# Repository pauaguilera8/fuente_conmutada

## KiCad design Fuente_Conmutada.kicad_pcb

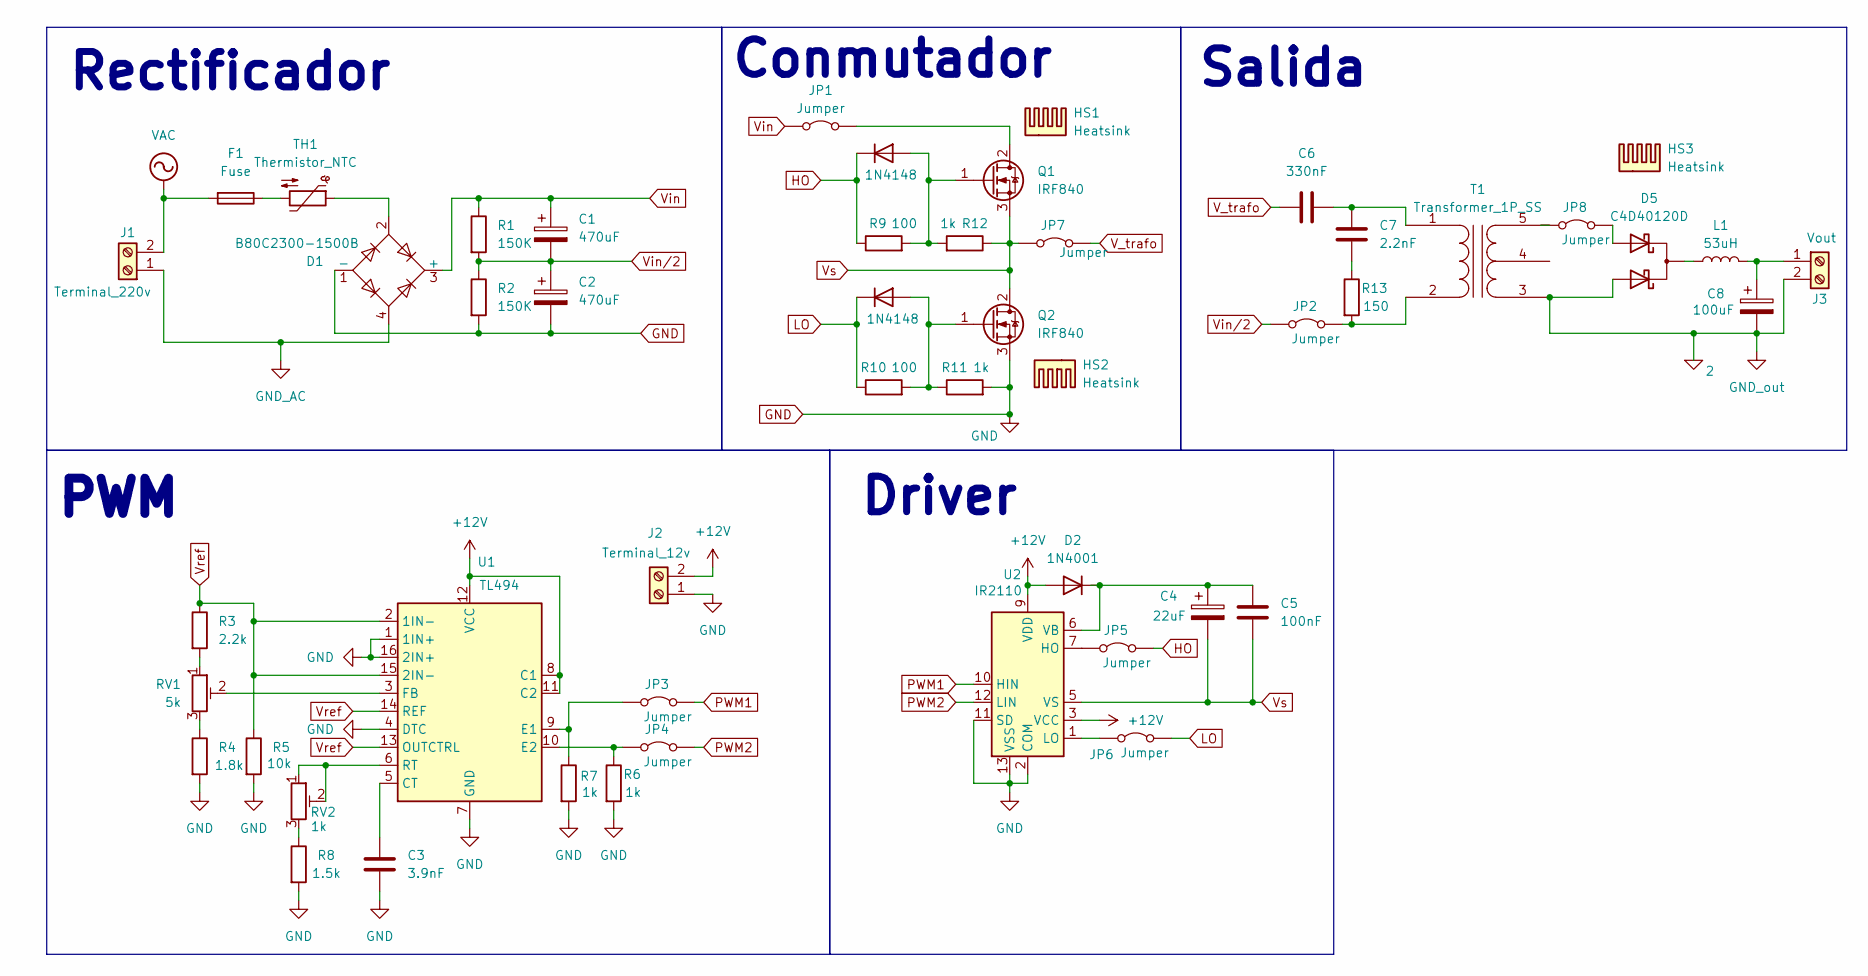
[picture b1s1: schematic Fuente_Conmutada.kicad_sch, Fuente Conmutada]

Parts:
C1, C2: 470uF; CP_Radial_D17.0mm_P7.50mm
C3: 3.9nF; C_Disc_D5.0mm_W2.5mm_P5.00mm
C4: 22uF; CP_Radial_D5.0mm_P2.00mm
C5: 100nF; C_Disc_D5.0mm_W2.5mm_P5.00mm
C6: 330nF; C_Disc_D5.0mm_W2.5mm_P5.00mm
C7: 2.2nF; C_Disc_D5.0mm_W2.5mm_P5.00mm
C8: 100uF; CP_Radial_D10.0mm_P5.00mm
D1: B80C2300-1500B; Diode_Bridge_Vishay_KBPM
D2: 1N4001; D_DO-35_SOD27_P7.62mm_Horizontal
D3, D4: 1N4148; D_DO-35_SOD27_P7.62mm_Horizontal
D5: C4D40120D; TO-220-3_Vertical
F1: Fuse; Fuseholder_Cylinder-5x20mm_Stelvio-Kontek_PTF78_Horizontal_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
HS1, HS2, HS3: Heatsink; Heatsink_Stonecold_HS-S02_13.21x9.53mm
J1: Terminal_220v; TerminalBlock_Altech_AK300-2_P5.00mm
J2: Terminal_12v; TerminalBlock_Altech_AK300-2_P5.00mm
J3: Vout; TerminalBlock_Altech_AK300-2_P5.00mm
JP1, JP2, JP3, JP4, JP5, JP6, JP7, JP8: Jumper; PinHeader_1x02_P2.54mm_Vertical
L1: 53uH; L_Toroid_Vertical_L22.4mm_W10.2mm_P7.90mm_Vishay_TJ4
Q1, Q2: IRF840; TO-220-3_Vertical
R1, R2: 150K; R_Axial_DIN0207_L6.3mm_D2.5mm_P10.16mm_Horizontal
R3: 2.2k; R_Axial_DIN0207_L6.3mm_D2.5mm_P10.16mm_Horizontal
R4: 1.8k; R_Axial_DIN0207_L6.3mm_D2.5mm_P10.16mm_Horizontal
R5: 10k; R_Axial_DIN0207_L6.3mm_D2.5mm_P10.16mm_Horizontal
R6, R7, R11, R12: 1k; R_Axial_DIN0207_L6.3mm_D2.5mm_P10.16mm_Horizontal
R8: 1.5k; R_Axial_DIN0207_L6.3mm_D2.5mm_P10.16mm_Horizontal
R9, R10: 100; R_Axial_DIN0207_L6.3mm_D2.5mm_P10.16mm_Horizontal
R13: 150; R_Axial_DIN0207_L6.3mm_D2.5mm_P10.16mm_Horizontal
RV1: 5k; Potentiometer_ACP_CA9-H2,5_Horizontal
RV2: 1k; Potentiometer_ACP_CA9-H2,5_Horizontal
T1: Transformer_1P_SS; Ferrite_Core_Trans
TH1: Thermistor_NTC; R_Axial_DIN0207_L6.3mm_D2.5mm_P7.62mm_Horizontal
U1: TL494; DIP-16_W7.62mm
U2: IR2110; DIP-14_W7.62mm

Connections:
+12V: D2.2 (A), J2.2, U1.8 (C1), U1.11 (C2), U1.12 (VCC), U2.3 (VCC), U2.9 (VDD)
/Punto_medio: JP2.2 (B), R13.2, T1.2 (AB)
GND: C2.2, C3.2, D1.1 (-), J2.1, Q2.3 (S), R2.2, R4.2, R5.2, R6.2, R7.2, R8.2, R11.2, U1.1 (1IN+), U1.4 (DTC), U1.7 (GND), U1.16 (2IN+), U2.2 (COM), U2.11 (SD), U2.13 (VSS)
GND_AC: D1.4, J1.1
HO: D3.1 (K), JP5.2 (B), R9.1
LO: D4.1 (K), JP6.2 (B), R10.1
unnamed: C7.2, R13.1
unnamed: C1.1, D1.3 (+), JP1.1 (A), R1.1
unnamed: D1.2, TH1.1
unnamed: C4.1, C5.1, D2.1 (K), U2.6 (VB)
unnamed: D3.2 (A), Q1.1 (G), R9.2, R12.2
unnamed: D4.2 (A), Q2.1 (G), R10.2, R11.1
unnamed: D5.1 (A1), JP8.2 (B)
unnamed: D5.2 (K), L1.1
unnamed: F1.1, TH1.2
unnamed: C8.1, J3.1, L1.2
unnamed: JP1.2 (B), Q1.2 (D)
unnamed: C1.2, C2.1, JP2.1 (A), R1.2, R2.1
unnamed: JP3.1 (A), R7.1, U1.9 (E1)
unnamed: JP4.1 (A), R6.1, U1.10 (E2)
unnamed: JP5.1 (A), U2.7 (HO)
unnamed: JP6.1 (A), U2.1 (LO)
unnamed: C6.2, JP7.2 (B)
unnamed: JP8.1 (A), T1.5 (SB)
unnamed: R3.2, RV1.1
unnamed: R4.1, RV1.3
unnamed: R8.1, RV2.3
unnamed: C6.1, C7.1, T1.1 (AA)
unnamed: C3.1, U1.5 (CT)
unnamed: RV1.2, U1.3 (FB)
unnamed: RV2.1, RV2.2, U1.6 (RT)
PWM1: JP3.2 (B), U2.10 (HIN)
PWM2: JP4.2 (B), U2.12 (LIN)
VAC: F1.2, J1.2
Vref: R3.1, R5.1, U1.2 (1IN-), U1.13 (OUTCTRL), U1.14 (REF), U1.15 (2IN-)
Vs: C4.2, C5.2, JP7.1 (A), Q1.3 (S), Q2.2 (D), R12.1, U2.5 (VS)

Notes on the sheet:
Salida
Rectificador
Driver
Conmutador
PWM

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
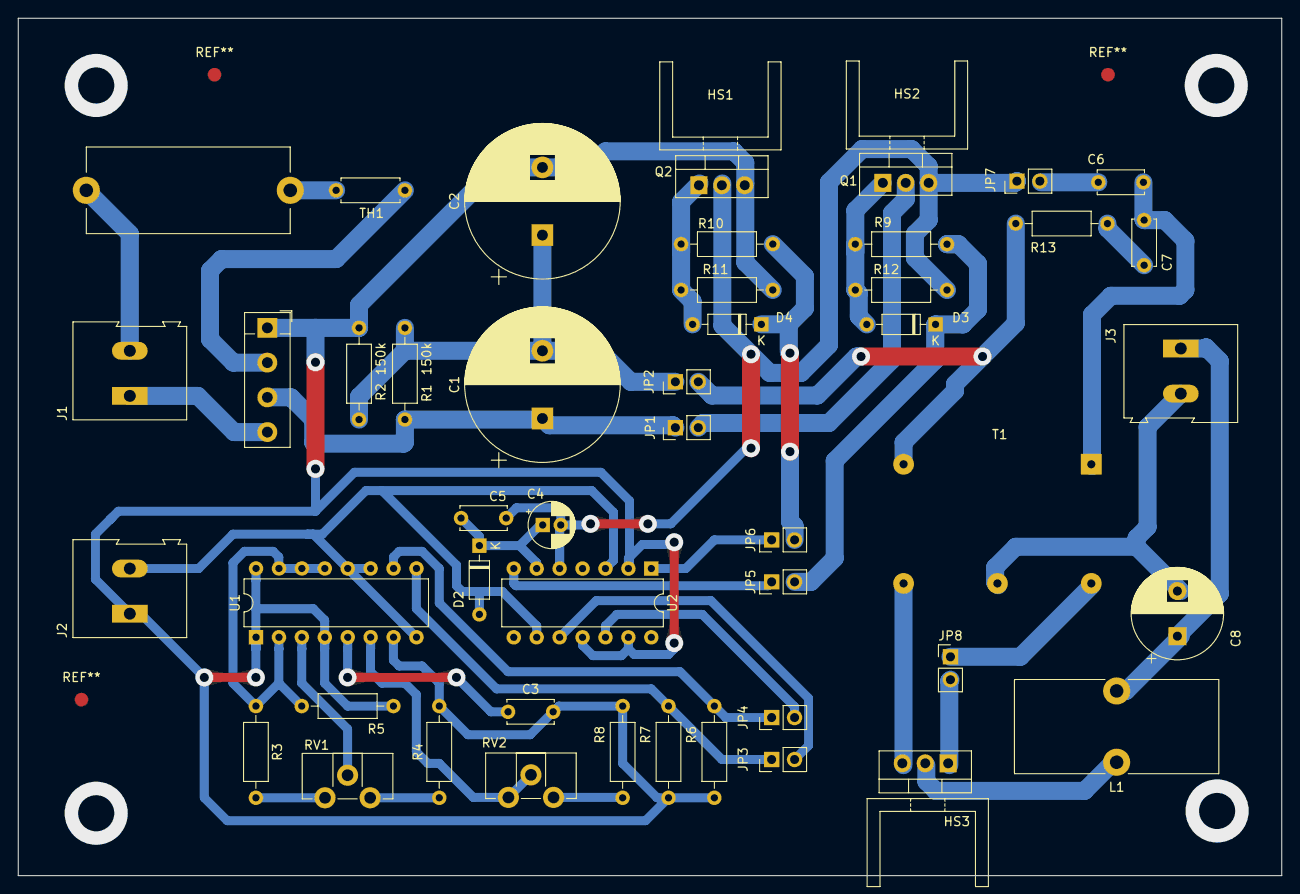
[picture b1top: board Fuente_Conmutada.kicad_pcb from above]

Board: 2 copper layers, 140.0 x 95.0 mm, 50 parts (0 on the bottom side), 38 nets.

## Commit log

2024-06-12 copia
2024-06-12 Footprints correctos agregados
    - Hice y puse el footprint del transformador
    - Corregí algunos otros footprints como el del puente de diodos por el que tenemos realmente y el portafusible
    - Actualicé los componentes eso en el editor de PCB y puse un cuadrado de 10x10cm donde se hace el PCB
2024-06-12 dawd
2024-06-12 Pinout de puente, tamaño de pads y no mucho mas
    -Cambié el pinout del puente por el que tenemos realmente
    -Cambié el tamaño de todos los pads a mínimo 2mm
    -Retoque en alguna que otra pista, casi nada
    Ahora hay varios warnings, que son porque el silkscreen choca con algo, pero no pasa nada crítico con eso
2024-06-13 Agregado de cosas
    Se agregó:
    - Pads de montaje
    - Footprints de disipadores para mosfets y rectificador de salida
    - Se puso en la capa correcta el choke de salida
2024-06-20 Agregado de disipadores
2024-06-29 test
    -Le hice test en el esquematico y pcb
2024-07-03 Esquemático
2024-07-04 fidu
    Se agregaron los fiduciales
2024-07-04 cambio
    saque un fidu
2024-07-04 Agregado de modelos 3D
2024-07-06 gerber
